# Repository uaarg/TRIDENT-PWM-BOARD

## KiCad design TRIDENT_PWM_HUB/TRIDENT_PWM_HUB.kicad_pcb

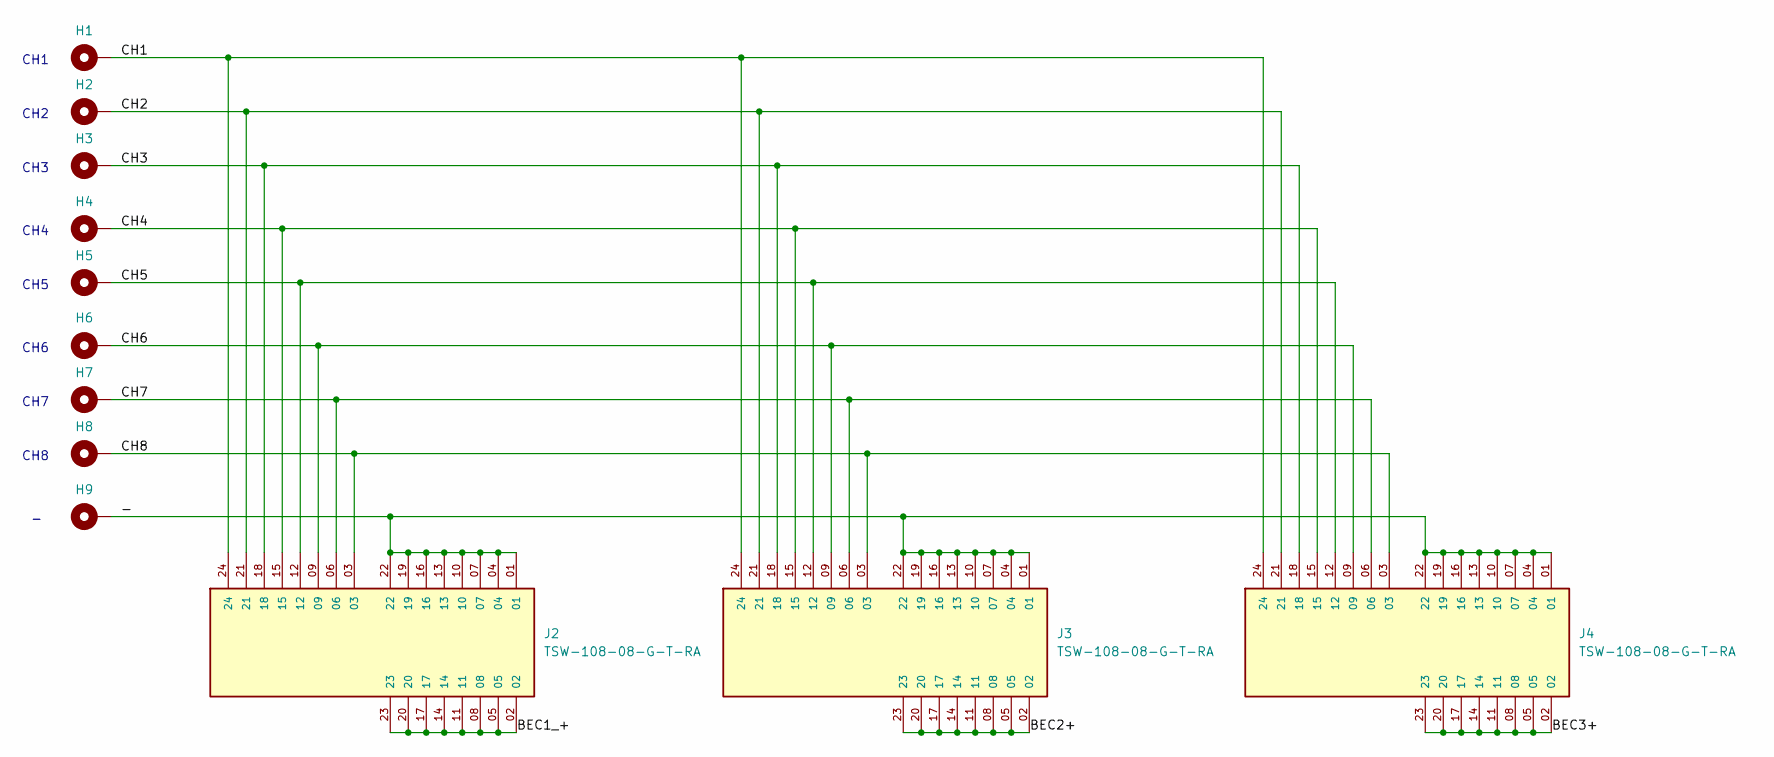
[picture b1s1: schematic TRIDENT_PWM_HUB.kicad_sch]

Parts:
H1, H2, H3, H4, H5, H6, H7, H8, H9: MountingHole_Pad; MountingHole_2.2mm_M2_DIN965_Pad_TopBottom
J2, J3, J4: TSW-108-08-G-T-RA; SAMTEC_TSW-108-08-G-T-RA; PARTREV R

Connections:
/-: H9.1, J2.01, J2.04, J2.07, J2.10, J2.13, J2.16, J2.19, J2.22, J3.01, J3.04, J3.07, J3.10, J3.13, J3.16, J3.19, J3.22, J4.01, J4.04, J4.07, J4.10, J4.13, J4.16, J4.19, J4.22
/CH1: H1.1, J2.24, J3.24, J4.24
/CH2: H2.1, J2.21, J3.21, J4.21
/CH3: H3.1, J2.18, J3.18, J4.18
/CH4: H4.1, J2.15, J3.15, J4.15
/CH5: H5.1, J2.12, J3.12, J4.12
/CH6: H6.1, J2.09, J3.09, J4.09
/CH7: H7.1, J2.06, J3.06, J4.06
/CH8: H8.1, J2.03, J3.03, J4.03
unnamed: J2.02, J2.05, J2.08, J2.11, J2.14, J2.17, J2.20, J2.23
unnamed: J3.02, J3.05, J3.08, J3.11, J3.14, J3.17, J3.20, J3.23
unnamed: J4.02, J4.05, J4.08, J4.11, J4.14, J4.17, J4.20, J4.23

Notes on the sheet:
CH1
CH7
CH4
CH2
CH3
CH8
CH6
CH5

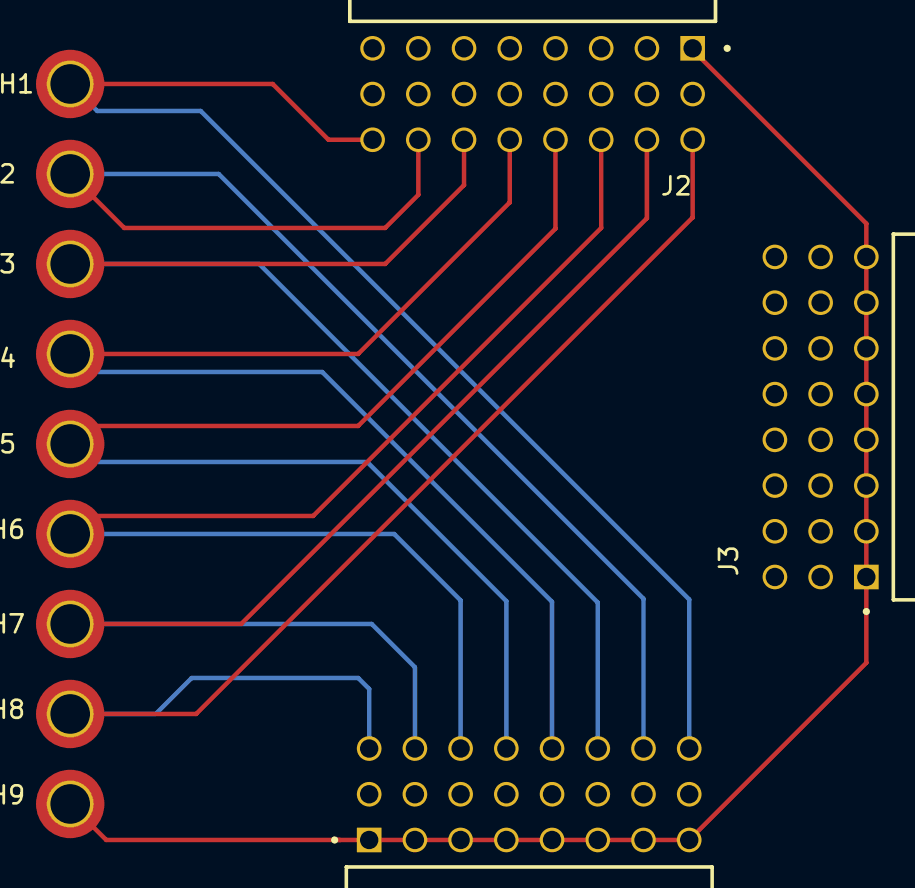
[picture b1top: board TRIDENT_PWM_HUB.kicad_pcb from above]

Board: 4 copper layers, 12 parts (0 on the bottom side), 12 nets.

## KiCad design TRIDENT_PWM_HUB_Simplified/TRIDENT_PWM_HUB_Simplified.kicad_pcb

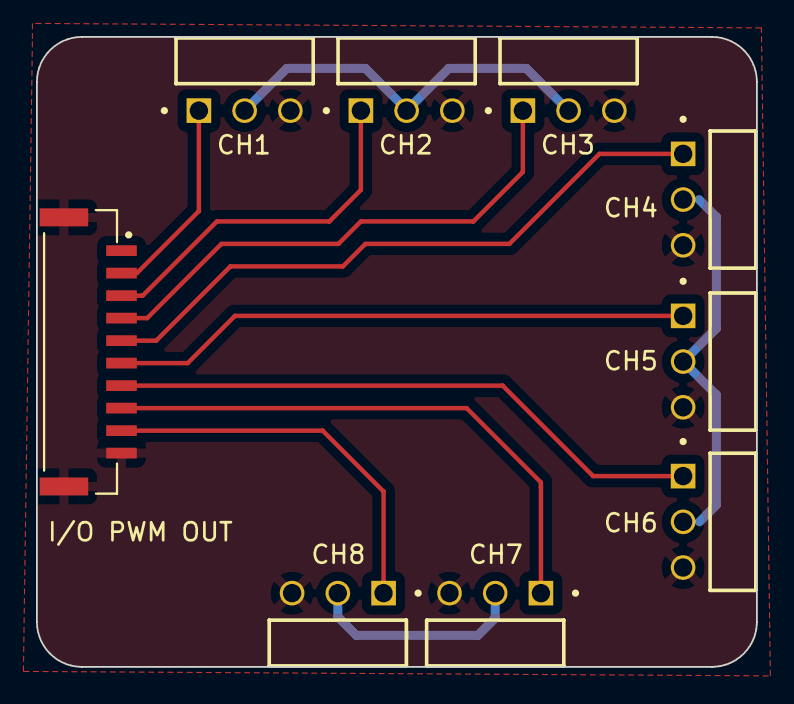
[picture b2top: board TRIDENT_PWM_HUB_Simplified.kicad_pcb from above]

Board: 2 copper layers, 40.0 x 35.0 mm, 9 parts (0 on the bottom side), 12 nets.

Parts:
CH1, CH2, CH3, CH4, CH5, CH6, CH7, CH8: Conn_01x03; SAMTEC_TSW-103-08-G-S-RA
I/O PWM OUT: SM10B-GHS-TB_LF__SN_; JST_SM10B-GHS-TB_LF__SN_

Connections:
/L_ESC_+: CH7.2, CH8.2
/R_ESC_+: CH1.2, CH2.2, CH3.2
/Rear_ESC_+: CH4.2, CH5.2, CH6.2
GND: CH1.3, CH2.3, CH3.3, CH4.3, CH5.3, CH6.3, CH7.3, CH8.3, I/O PWM OUT.10, I/O PWM OUT.S1 (SHIELD), I/O PWM OUT.S2 (SHIELD)
unnamed: CH1.1, I/O PWM OUT.2
unnamed: CH2.1, I/O PWM OUT.3
unnamed: CH3.1, I/O PWM OUT.4
unnamed: CH4.1, I/O PWM OUT.5
unnamed: CH5.1, I/O PWM OUT.6
unnamed: CH6.1, I/O PWM OUT.7
unnamed: CH7.1, I/O PWM OUT.8
unnamed: CH8.1, I/O PWM OUT.9
